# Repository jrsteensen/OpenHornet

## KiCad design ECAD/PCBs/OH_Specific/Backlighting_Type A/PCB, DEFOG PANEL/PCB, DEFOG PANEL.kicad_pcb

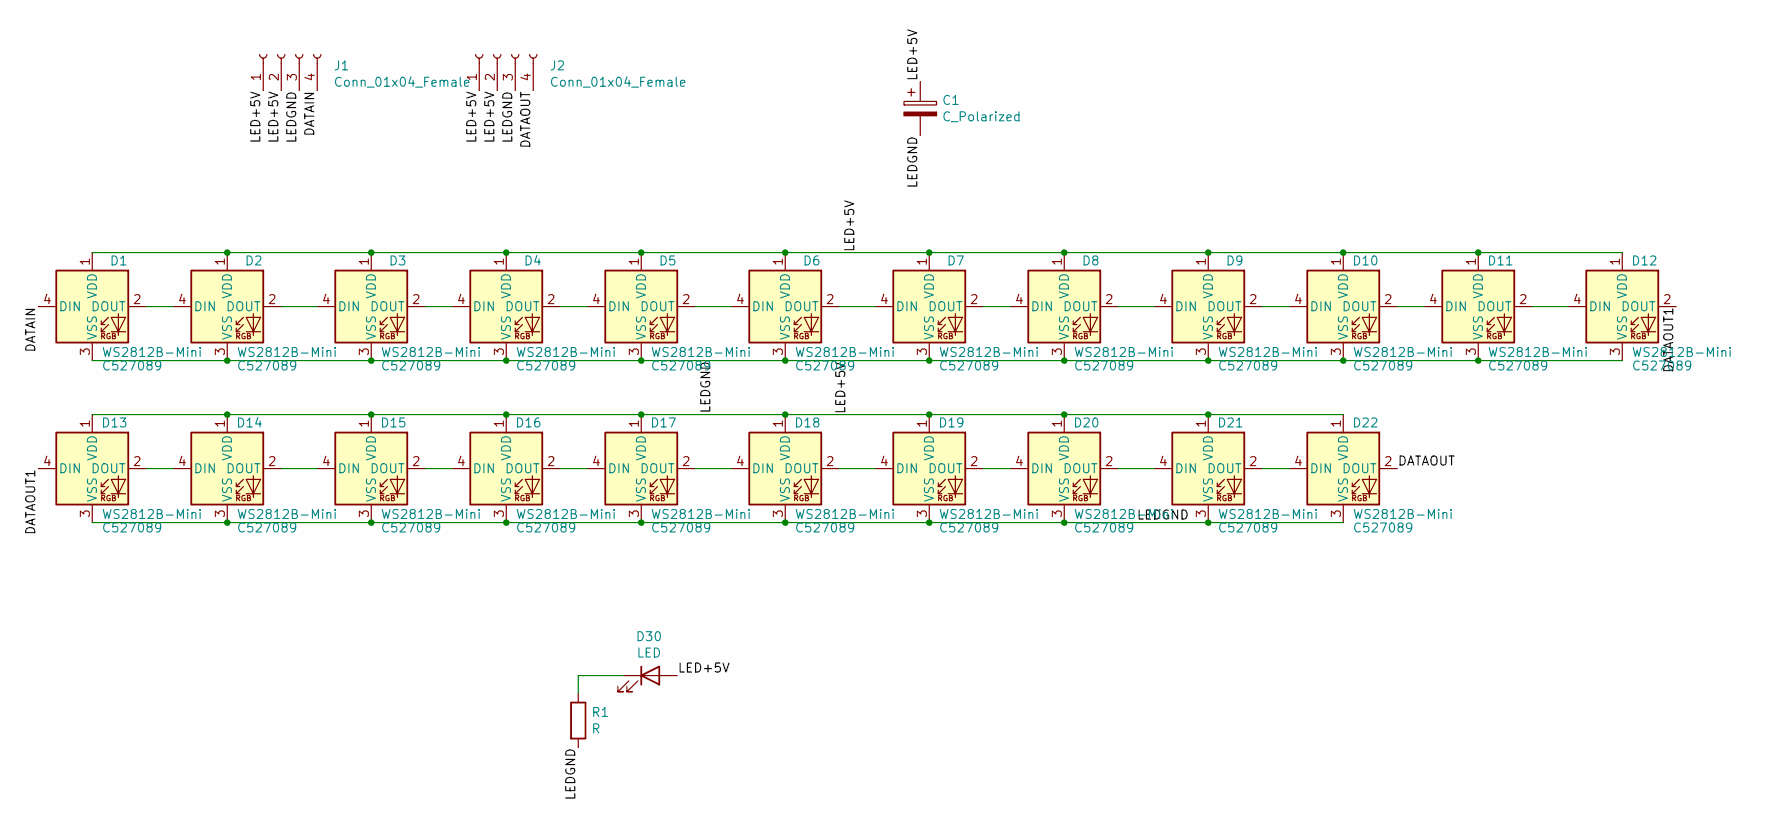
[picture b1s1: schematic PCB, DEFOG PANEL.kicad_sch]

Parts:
C1: C_Polarized; CP_Elec_8x10; LCSC C445083
D1, D2, D3, D4, D5, D6, D7, D8, D9, D10, D11, D12, D13, D14, D15, D16, D17, D18, D19, D20, D21, D22: WS2812B-Mini; LED_WS2812B-MINI_PLCC4_3.5x3.5mm_P1.75mm; LCSC Part Number C527089
D30: LED; LED_D3.0mm
J1, J2: Conn_01x04_Female; Molex_Mini-Fit_Jr_5566-04A_2x02_P4.20mm_Vertical; LCSC C293502
R1: R; R_0603_1608Metric; LCSC C23179

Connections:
/DATAIN: D1.4 (DIN), J1.4
/DATAOUT: D22.2 (DOUT), J2.4
/DATAOUT1: D12.2 (DOUT), D13.4 (DIN)
/LED+5V: C1.1, D1.1 (VDD), D2.1 (VDD), D3.1 (VDD), D4.1 (VDD), D5.1 (VDD), D6.1 (VDD), D7.1 (VDD), D8.1 (VDD), D9.1 (VDD), D10.1 (VDD), D11.1 (VDD), D12.1 (VDD), D13.1 (VDD), D14.1 (VDD), D15.1 (VDD), D16.1 (VDD), D17.1 (VDD), D18.1 (VDD), D19.1 (VDD), D20.1 (VDD), D21.1 (VDD), D22.1 (VDD), D30.2 (A), J1.1, J1.2, J2.1, J2.2
/LEDGND: C1.2, D1.3 (VSS), D2.3 (VSS), D3.3 (VSS), D4.3 (VSS), D5.3 (VSS), D6.3 (VSS), D7.3 (VSS), D8.3 (VSS), D9.3 (VSS), D10.3 (VSS), D11.3 (VSS), D12.3 (VSS), D13.3 (VSS), D14.3 (VSS), D15.3 (VSS), D16.3 (VSS), D17.3 (VSS), D18.3 (VSS), D19.3 (VSS), D20.3 (VSS), D21.3 (VSS), D22.3 (VSS), J1.3, J2.3, R1.2
unnamed: D1.2 (DOUT), D2.4 (DIN)
unnamed: D2.2 (DOUT), D3.4 (DIN)
unnamed: D3.2 (DOUT), D4.4 (DIN)
unnamed: D4.2 (DOUT), D5.4 (DIN)
unnamed: D5.2 (DOUT), D6.4 (DIN)
unnamed: D6.2 (DOUT), D7.4 (DIN)
unnamed: D7.2 (DOUT), D8.4 (DIN)
unnamed: D8.2 (DOUT), D9.4 (DIN)
unnamed: D10.2 (DOUT), D11.4 (DIN)
unnamed: D9.2 (DOUT), D10.4 (DIN)
unnamed: D11.2 (DOUT), D12.4 (DIN)
unnamed: D13.2 (DOUT), D14.4 (DIN)
unnamed: D14.2 (DOUT), D15.4 (DIN)
unnamed: D15.2 (DOUT), D16.4 (DIN)
unnamed: D16.2 (DOUT), D17.4 (DIN)
unnamed: D17.2 (DOUT), D18.4 (DIN)
unnamed: D18.2 (DOUT), D19.4 (DIN)
unnamed: D19.2 (DOUT), D20.4 (DIN)
unnamed: D20.2 (DOUT), D21.4 (DIN)
unnamed: D21.2 (DOUT), D22.4 (DIN)
unnamed: D30.1 (K), R1.1

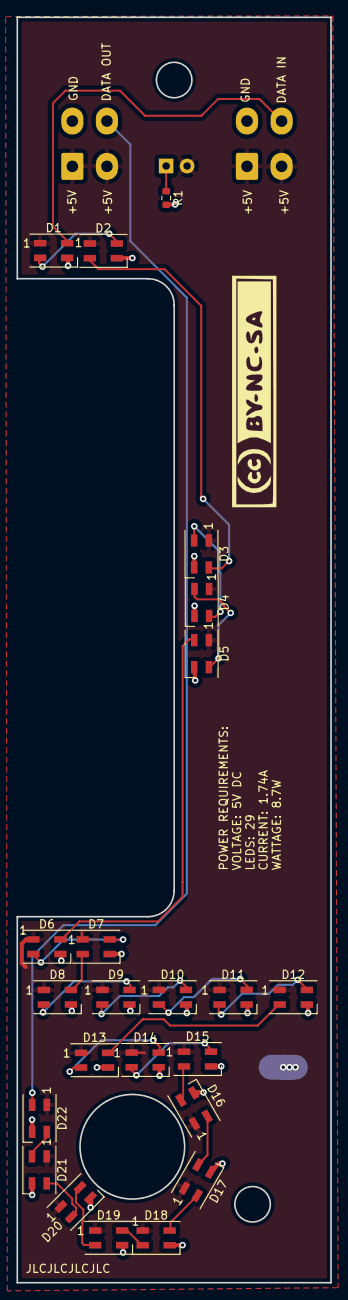
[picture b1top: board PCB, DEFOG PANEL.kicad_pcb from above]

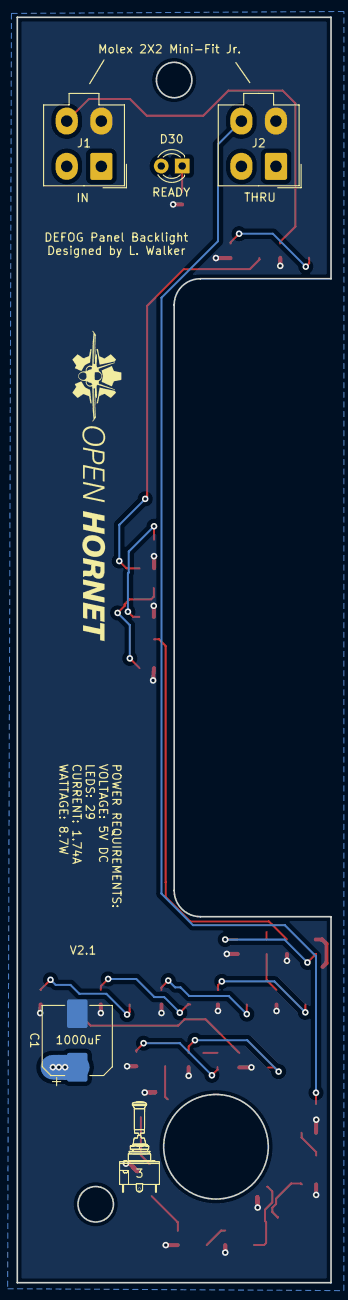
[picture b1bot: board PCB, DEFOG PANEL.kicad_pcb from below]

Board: 2 copper layers, 38.1 x 153.7 mm, 30 parts (5 on the bottom side), 26 nets.

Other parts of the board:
G1: LOGO; CC-BY-NC-SA-Small
G2: S3AL Toggle; S3AL_Toggle_Silkscreen
G3: LOGO; OH_LOGO_37.7mm_5.9mm

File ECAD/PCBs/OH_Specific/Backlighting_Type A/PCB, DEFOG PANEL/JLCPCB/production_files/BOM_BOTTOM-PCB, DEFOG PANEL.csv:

Comment,Designator,Footprint,LCSC
Conn_01x04_Female,"J1,J2",Molex_Mini-Fit_Jr_5566-04A_2x02_P4.20mm_Vertical,C293502
C_Polarized,C1,CP_Elec_8x10,C445083
LED,D30,LED_D3.0mm,

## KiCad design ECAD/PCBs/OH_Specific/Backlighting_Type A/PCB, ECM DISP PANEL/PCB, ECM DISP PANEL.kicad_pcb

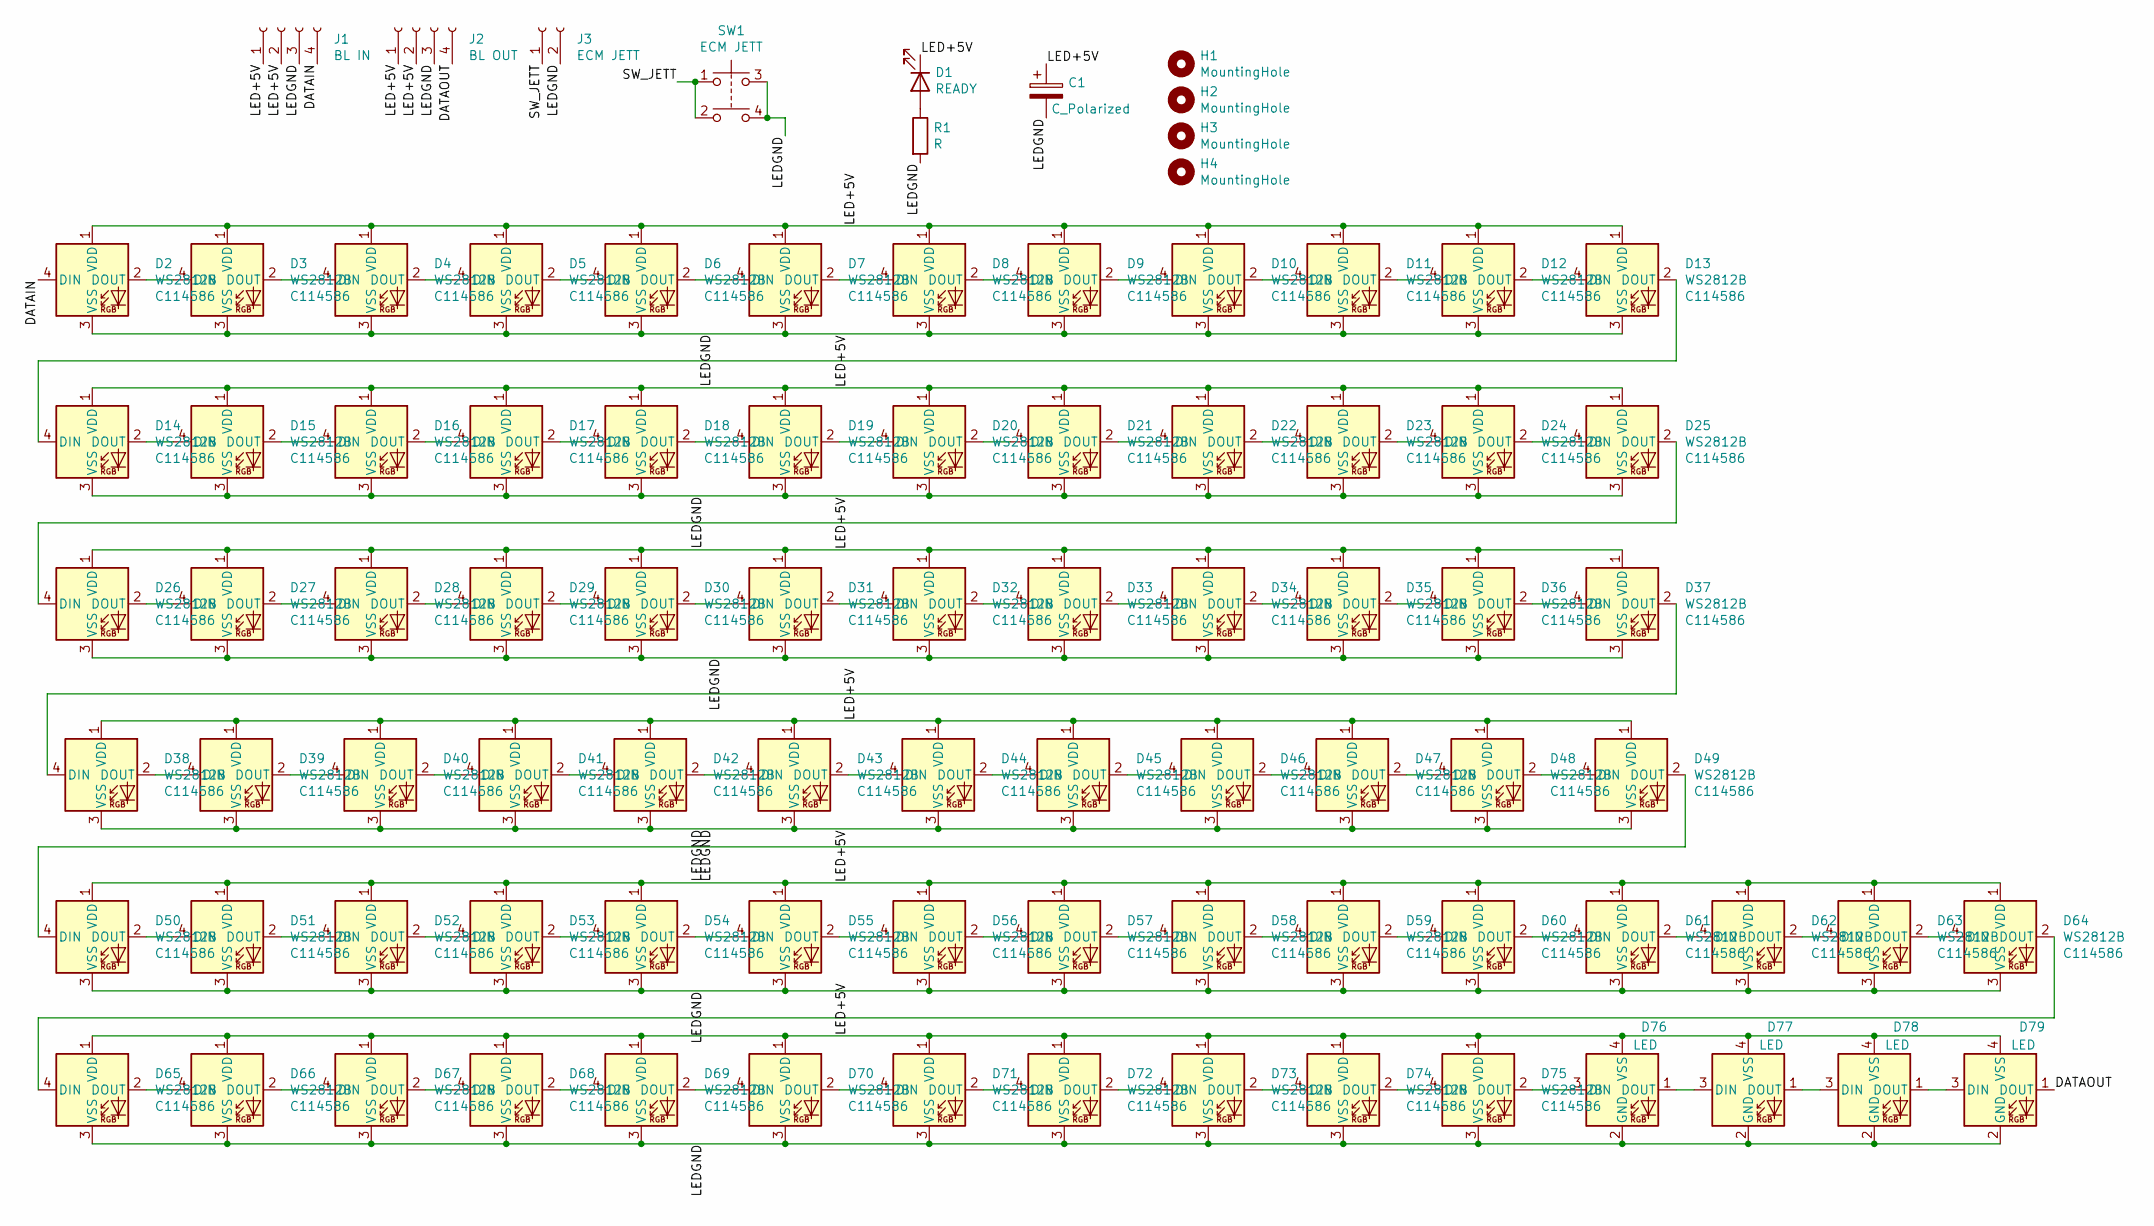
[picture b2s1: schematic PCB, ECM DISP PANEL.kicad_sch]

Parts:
C1: C_Polarized; CP_Elec_8x10
D1: READY; LED_D3.0mm
D2, D3, D4, D5, D6, D7, D8, D9, D10, D11, D12, D13, D14, D15, D16, D17, D18, D19, D20, D21, D22, D23, D24, D25, D26, D27, D28, D29, D30, D31, D32, D33, D34, D35, D36, D37, D38, D39, D40, D41, D42, D43, D44, D45, D46, D47, D48, D49, D50, D51, D52, D53, D54, D55, D56, D57, D58, D59, D60, D61, D62, D63, D64, D65, D66, D67, D68, D69, D70, D71, D72, D73, D74, D75: WS2812B; LED_WS2812B_PLCC4_5.0x5.0mm_P3.2mm; LCSC Part Number C114586
D76, D77, D78, D79: LED; WS2812-2020; LCSC C965555
H1, H2, H3, H4: MountingHole; MountingHole_4.5mm_Pad
J1: BL IN; Molex_Mini-Fit_Jr_5566-04A_2x02_P4.20mm_Vertical
J2: BL OUT; Molex_Mini-Fit_Jr_5566-04A_2x02_P4.20mm_Vertical
J3: ECM JETT; Molex_KK-254_AE-6410-02A_1x02_P2.54mm_Vertical
R1: R; R_0603_1608Metric; LCSC C23138
SW1: ECM JETT; SW_TH_Tactile_Omron_B3F-10xx

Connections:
/DATAIN: D2.4 (DIN), J1.4
/DATAOUT: D79.1 (DOUT), J2.4
/LED+5V: C1.1, D1.1 (K), D2.1 (VDD), D3.1 (VDD), D4.1 (VDD), D5.1 (VDD), D6.1 (VDD), D7.1 (VDD), D8.1 (VDD), D9.1 (VDD), D10.1 (VDD), D11.1 (VDD), D12.1 (VDD), D13.1 (VDD), D14.1 (VDD), D15.1 (VDD), D16.1 (VDD), D17.1 (VDD), D18.1 (VDD), D19.1 (VDD), D20.1 (VDD), D21.1 (VDD), D22.1 (VDD), D23.1 (VDD), D24.1 (VDD), D25.1 (VDD), D26.1 (VDD), D27.1 (VDD), D28.1 (VDD), D29.1 (VDD), D30.1 (VDD), D31.1 (VDD), D32.1 (VDD), D33.1 (VDD), D34.1 (VDD), D35.1 (VDD), D36.1 (VDD), D37.1 (VDD), D38.1 (VDD), D39.1 (VDD), D40.1 (VDD), D41.1 (VDD), D42.1 (VDD), D43.1 (VDD), D44.1 (VDD), D45.1 (VDD), D46.1 (VDD), D47.1 (VDD), D48.1 (VDD), D49.1 (VDD), D50.1 (VDD), D51.1 (VDD), D52.1 (VDD), D53.1 (VDD), D54.1 (VDD), D55.1 (VDD), D56.1 (VDD), D57.1 (VDD), D58.1 (VDD), D59.1 (VDD), D60.1 (VDD), D61.1 (VDD), D62.1 (VDD), D63.1 (VDD), D64.1 (VDD), D65.1 (VDD), D66.1 (VDD), D67.1 (VDD), D68.1 (VDD), D69.1 (VDD), D70.1 (VDD), D71.1 (VDD), D72.1 (VDD), D73.1 (VDD), D74.1 (VDD), D75.1 (VDD), D76.4 (VSS), D77.4 (VSS), D78.4 (VSS), D79.4 (VSS), J1.1, J1.2, J2.1, J2.2
/LEDGND: C1.2, D2.3 (VSS), D3.3 (VSS), D4.3 (VSS), D5.3 (VSS), D6.3 (VSS), D7.3 (VSS), D8.3 (VSS), D9.3 (VSS), D10.3 (VSS), D11.3 (VSS), D12.3 (VSS), D13.3 (VSS), D14.3 (VSS), D15.3 (VSS), D16.3 (VSS), D17.3 (VSS), D18.3 (VSS), D19.3 (VSS), D20.3 (VSS), D21.3 (VSS), D22.3 (VSS), D23.3 (VSS), D24.3 (VSS), D25.3 (VSS), D26.3 (VSS), D27.3 (VSS), D28.3 (VSS), D29.3 (VSS), D30.3 (VSS), D31.3 (VSS), D32.3 (VSS), D33.3 (VSS), D34.3 (VSS), D35.3 (VSS), D36.3 (VSS), D37.3 (VSS), D38.3 (VSS), D39.3 (VSS), D40.3 (VSS), D41.3 (VSS), D42.3 (VSS), D43.3 (VSS), D44.3 (VSS), D45.3 (VSS), D46.3 (VSS), D47.3 (VSS), D48.3 (VSS), D49.3 (VSS), D50.3 (VSS), D51.3 (VSS), D52.3 (VSS), D53.3 (VSS), D54.3 (VSS), D55.3 (VSS), D56.3 (VSS), D57.3 (VSS), D58.3 (VSS), D59.3 (VSS), D60.3 (VSS), D61.3 (VSS), D62.3 (VSS), D63.3 (VSS), D64.3 (VSS), D65.3 (VSS), D66.3 (VSS), D67.3 (VSS), D68.3 (VSS), D69.3 (VSS), D70.3 (VSS), D71.3 (VSS), D72.3 (VSS), D73.3 (VSS), D74.3 (VSS), D75.3 (VSS), D76.2 (GND), D77.2 (GND), D78.2 (GND), D79.2 (GND), J1.3, J2.3, J3.2, R1.2, SW1.3, SW1.4
/SW_JETT: J3.1, SW1.1, SW1.2
unnamed: D1.2 (A), R1.1
unnamed: D2.2 (DOUT), D3.4 (DIN)
unnamed: D3.2 (DOUT), D4.4 (DIN)
unnamed: D4.2 (DOUT), D5.4 (DIN)
unnamed: D5.2 (DOUT), D6.4 (DIN)
unnamed: D6.2 (DOUT), D7.4 (DIN)
unnamed: D7.2 (DOUT), D8.4 (DIN)
unnamed: D8.2 (DOUT), D9.4 (DIN)
unnamed: D10.2 (DOUT), D11.4 (DIN)
unnamed: D9.2 (DOUT), D10.4 (DIN)
unnamed: D11.2 (DOUT), D12.4 (DIN)
unnamed: D12.2 (DOUT), D13.4 (DIN)
unnamed: D13.2 (DOUT), D14.4 (DIN)
unnamed: D14.2 (DOUT), D15.4 (DIN)
unnamed: D15.2 (DOUT), D16.4 (DIN)
unnamed: D16.2 (DOUT), D17.4 (DIN)
unnamed: D17.2 (DOUT), D18.4 (DIN)
unnamed: D18.2 (DOUT), D19.4 (DIN)
unnamed: D19.2 (DOUT), D20.4 (DIN)
unnamed: D20.2 (DOUT), D21.4 (DIN)
unnamed: D21.2 (DOUT), D22.4 (DIN)
unnamed: D22.2 (DOUT), D23.4 (DIN)
unnamed: D23.2 (DOUT), D24.4 (DIN)
unnamed: D24.2 (DOUT), D25.4 (DIN)
unnamed: D25.2 (DOUT), D26.4 (DIN)
unnamed: D26.2 (DOUT), D27.4 (DIN)
unnamed: D27.2 (DOUT), D28.4 (DIN)
unnamed: D28.2 (DOUT), D29.4 (DIN)
unnamed: D29.2 (DOUT), D30.4 (DIN)
unnamed: D30.2 (DOUT), D31.4 (DIN)
unnamed: D31.2 (DOUT), D32.4 (DIN)
unnamed: D32.2 (DOUT), D33.4 (DIN)
unnamed: D33.2 (DOUT), D34.4 (DIN)
unnamed: D34.2 (DOUT), D35.4 (DIN)
unnamed: D35.2 (DOUT), D36.4 (DIN)
unnamed: D36.2 (DOUT), D37.4 (DIN)
unnamed: D37.2 (DOUT), D38.4 (DIN)
unnamed: D38.2 (DOUT), D39.4 (DIN)
unnamed: D39.2 (DOUT), D40.4 (DIN)
unnamed: D40.2 (DOUT), D41.4 (DIN)
unnamed: D41.2 (DOUT), D42.4 (DIN)
unnamed: D42.2 (DOUT), D43.4 (DIN)
unnamed: D43.2 (DOUT), D44.4 (DIN)
unnamed: D44.2 (DOUT), D45.4 (DIN)
unnamed: D45.2 (DOUT), D46.4 (DIN)
unnamed: D46.2 (DOUT), D47.4 (DIN)
unnamed: D47.2 (DOUT), D48.4 (DIN)
unnamed: D48.2 (DOUT), D49.4 (DIN)
unnamed: D49.2 (DOUT), D50.4 (DIN)
unnamed: D50.2 (DOUT), D51.4 (DIN)
unnamed: D51.2 (DOUT), D52.4 (DIN)
unnamed: D52.2 (DOUT), D53.4 (DIN)
unnamed: D53.2 (DOUT), D54.4 (DIN)
unnamed: D54.2 (DOUT), D55.4 (DIN)
unnamed: D55.2 (DOUT), D56.4 (DIN)
unnamed: D56.2 (DOUT), D57.4 (DIN)
unnamed: D57.2 (DOUT), D58.4 (DIN)
unnamed: D58.2 (DOUT), D59.4 (DIN)
unnamed: D59.2 (DOUT), D60.4 (DIN)
unnamed: D60.2 (DOUT), D61.4 (DIN)
unnamed: D61.2 (DOUT), D62.4 (DIN)
unnamed: D62.2 (DOUT), D63.4 (DIN)
unnamed: D63.2 (DOUT), D64.4 (DIN)
unnamed: D64.2 (DOUT), D65.4 (DIN)
unnamed: D65.2 (DOUT), D66.4 (DIN)
unnamed: D66.2 (DOUT), D67.4 (DIN)
unnamed: D67.2 (DOUT), D68.4 (DIN)
unnamed: D68.2 (DOUT), D69.4 (DIN)
unnamed: D69.2 (DOUT), D70.4 (DIN)
unnamed: D70.2 (DOUT), D71.4 (DIN)
unnamed: D71.2 (DOUT), D72.4 (DIN)
unnamed: D72.2 (DOUT), D73.4 (DIN)
unnamed: D73.2 (DOUT), D74.4 (DIN)
unnamed: D74.2 (DOUT), D75.4 (DIN)
unnamed: D75.2 (DOUT), D76.3 (DIN)
unnamed: D76.1 (DOUT), D77.3 (DIN)
unnamed: D77.1 (DOUT), D78.3 (DIN)
unnamed: D78.1 (DOUT), D79.3 (DIN)

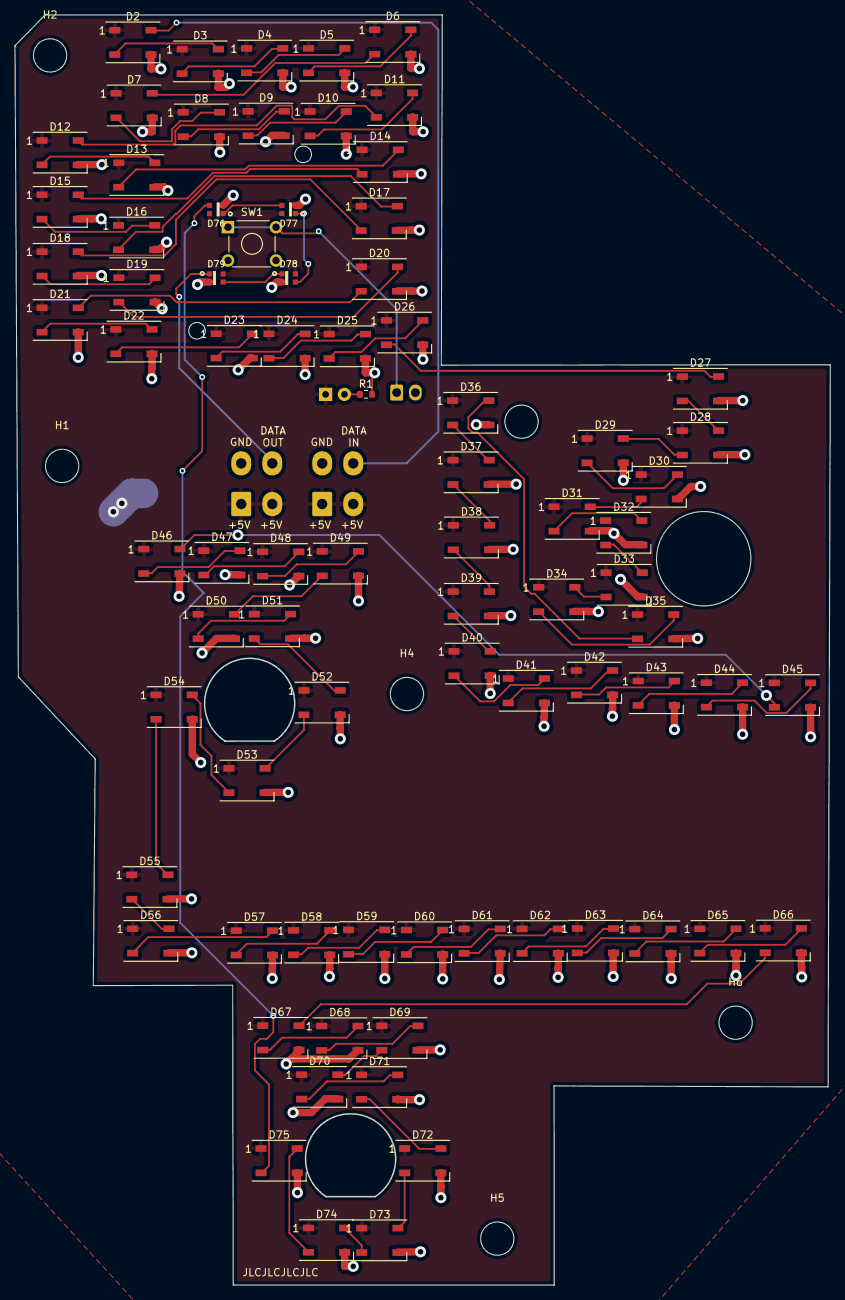
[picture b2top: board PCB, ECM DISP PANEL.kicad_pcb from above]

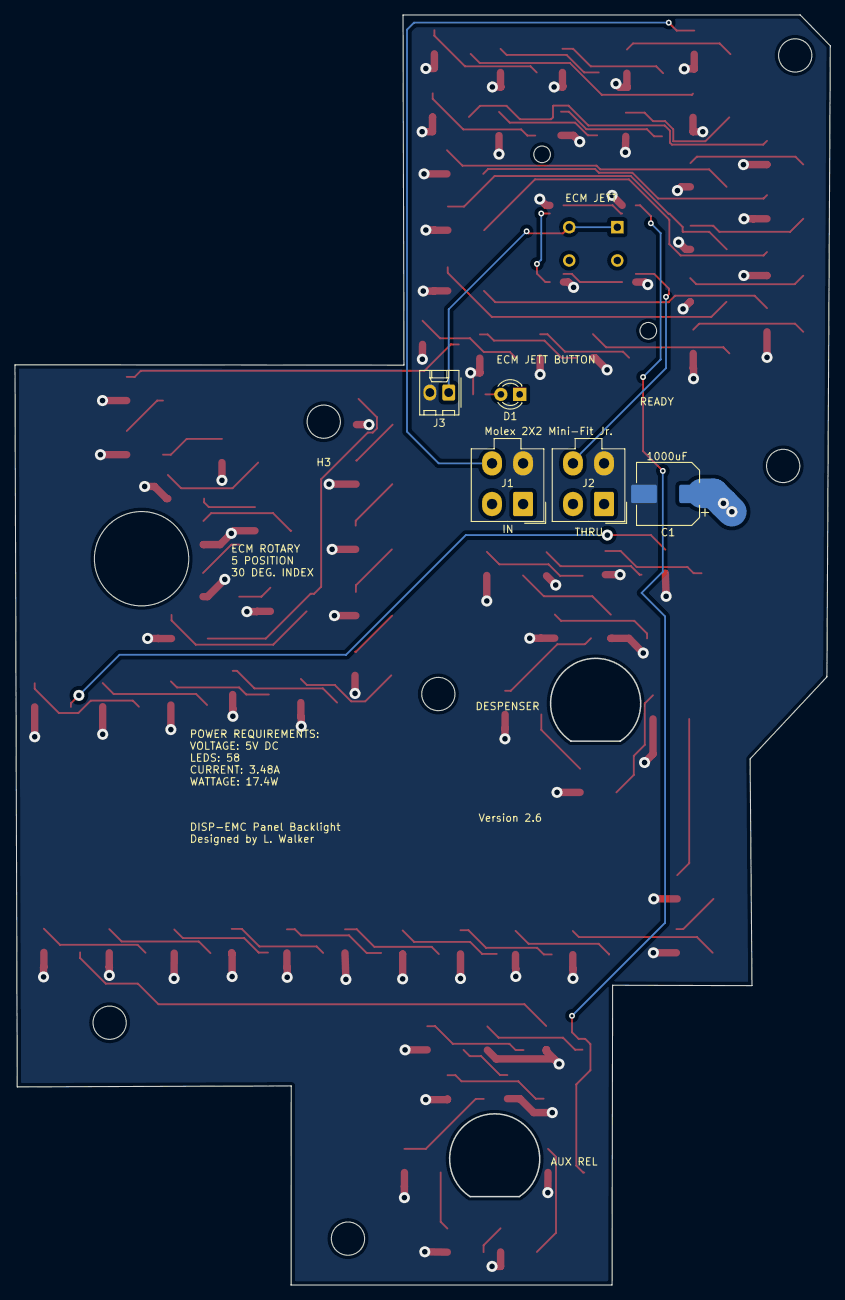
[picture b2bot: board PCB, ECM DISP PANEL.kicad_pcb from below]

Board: 2 copper layers, 110.3 x 171.8 mm, 91 parts (6 on the bottom side), 83 nets.

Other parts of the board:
H5, H6: MountingHole; MountingHole_4.5mm

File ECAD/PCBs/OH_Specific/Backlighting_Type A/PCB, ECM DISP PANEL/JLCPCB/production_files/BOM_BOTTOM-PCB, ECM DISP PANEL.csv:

Comment,Designator,Footprint,LCSC
ECM JETT,J3,Molex_KK-254_AE-6410-02A_1x02_P2.54mm_Vertical,C293316
BL IN,"J1,J2",Molex_Mini-Fit_Jr_5566-04A_2x02_P4.20mm_Vertical,C293502
1000 nF,C1,CP_Elec_8x10,C445083
READY,D1,LED_D3.0mm,

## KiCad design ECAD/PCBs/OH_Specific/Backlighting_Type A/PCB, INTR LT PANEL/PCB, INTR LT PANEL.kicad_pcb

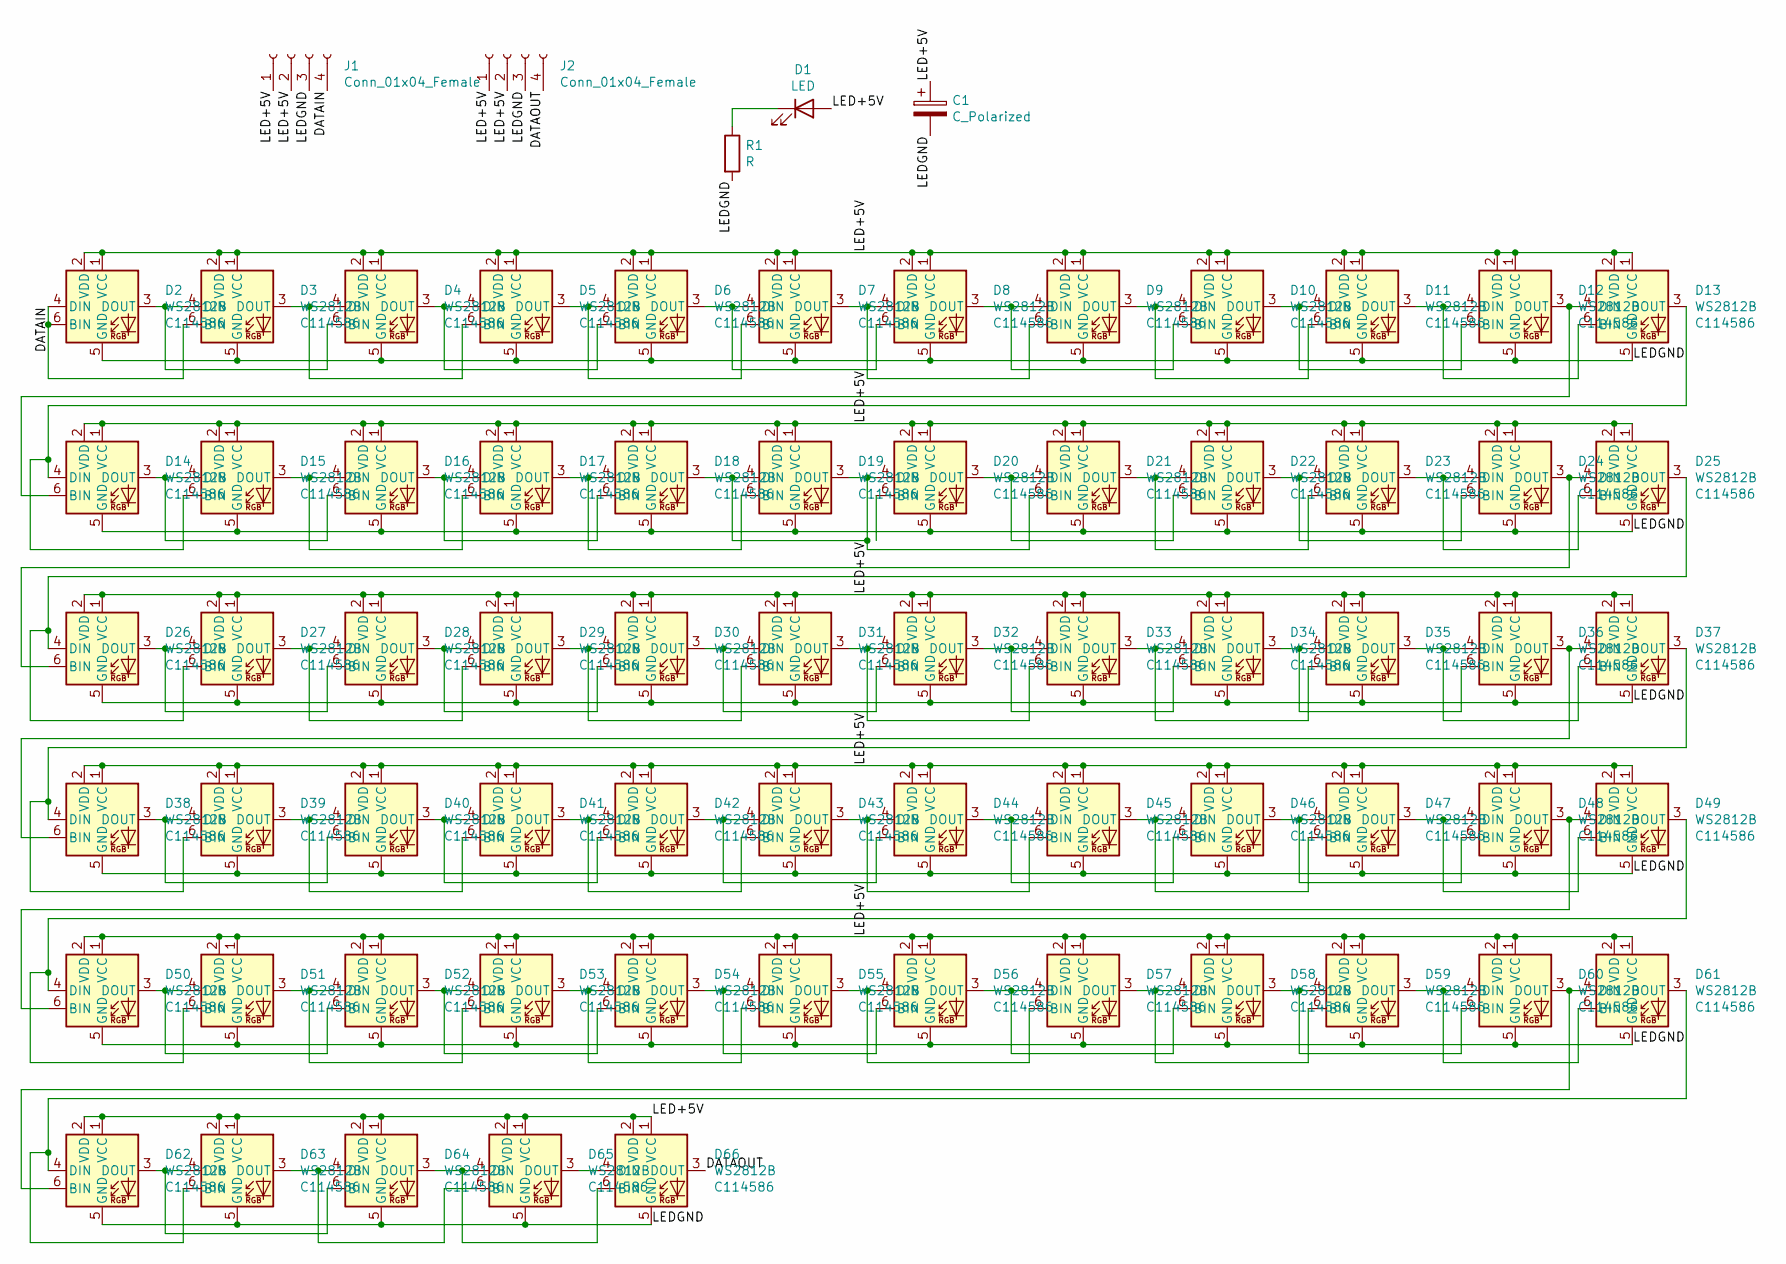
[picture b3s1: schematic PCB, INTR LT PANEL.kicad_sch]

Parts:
C1: C_Polarized; CP_Elec_8x10
D1: LED; LED_D3.0mm
D2, D3, D4, D5, D6, D7, D8, D9, D10, D11, D12, D13, D14, D15, D16, D17, D18, D19, D20, D21, D22, D23, D24, D25, D26, D27, D28, D29, D30, D31, D32, D33, D34, D35, D36, D37, D38, D39, D40, D41, D42, D43, D44, D45, D46, D47, D48, D49, D50, D51, D52, D53, D54, D55, D56, D57, D58, D59, D60, D61, D62, D63, D64, D65, D66: WS2812B; LED_WS2812_PLCC6_5.0x5.0mm_P1.6mm; LCSC Part Number C114586
J1, J2: Conn_01x04_Female; Molex_Mini-Fit_Jr_5566-04A_2x02_P4.20mm_Vertical
R1: R; R_0603_1608Metric

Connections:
/DATAIN: D2.4 (DIN), D2.6 (BIN), D3.6 (BIN), J1.4
/DATAOUT: D66.3 (DOUT), J2.4
/LED+5V: C1.1, D1.2 (A), D2.1 (VCC), D2.2 (VDD), D3.1 (VCC), D3.2 (VDD), D4.1 (VCC), D4.2 (VDD), D5.1 (VCC), D5.2 (VDD), D6.1 (VCC), D6.2 (VDD), D7.1 (VCC), D7.2 (VDD), D8.1 (VCC), D8.2 (VDD), D9.1 (VCC), D9.2 (VDD), D10.1 (VCC), D10.2 (VDD), D11.1 (VCC), D11.2 (VDD), D12.1 (VCC), D12.2 (VDD), D13.1 (VCC), D13.2 (VDD), D14.1 (VCC), D14.2 (VDD), D15.1 (VCC), D15.2 (VDD), D16.1 (VCC), D16.2 (VDD), D17.1 (VCC), D17.2 (VDD), D18.1 (VCC), D18.2 (VDD), D19.1 (VCC), D19.2 (VDD), D20.1 (VCC), D20.2 (VDD), D21.1 (VCC), D21.2 (VDD), D22.1 (VCC), D22.2 (VDD), D23.1 (VCC), D23.2 (VDD), D24.1 (VCC), D24.2 (VDD), D25.1 (VCC), D25.2 (VDD), D26.1 (VCC), D26.2 (VDD), D27.1 (VCC), D27.2 (VDD), D28.1 (VCC), D28.2 (VDD), D29.1 (VCC), D29.2 (VDD), D30.1 (VCC), D30.2 (VDD), D31.1 (VCC), D31.2 (VDD), D32.1 (VCC), D32.2 (VDD), D33.1 (VCC), D33.2 (VDD), D34.1 (VCC), D34.2 (VDD), D35.1 (VCC), D35.2 (VDD), D36.1 (VCC), D36.2 (VDD), D37.1 (VCC), D37.2 (VDD), D38.1 (VCC), D38.2 (VDD), D39.1 (VCC), D39.2 (VDD), D40.1 (VCC), D40.2 (VDD), D41.1 (VCC), D41.2 (VDD), D42.1 (VCC), D42.2 (VDD), D43.1 (VCC), D43.2 (VDD), D44.1 (VCC), D44.2 (VDD), D45.1 (VCC), D45.2 (VDD), D46.1 (VCC), D46.2 (VDD), D47.1 (VCC), D47.2 (VDD), D48.1 (VCC), D48.2 (VDD), D49.1 (VCC), D49.2 (VDD), D50.1 (VCC), D50.2 (VDD), D51.1 (VCC), D51.2 (VDD), D52.1 (VCC), D52.2 (VDD), D53.1 (VCC), D53.2 (VDD), D54.1 (VCC), D54.2 (VDD), D55.1 (VCC), D55.2 (VDD), D56.1 (VCC), D56.2 (VDD), D57.1 (VCC), D57.2 (VDD), D58.1 (VCC), D58.2 (VDD), D59.1 (VCC), D59.2 (VDD), D60.1 (VCC), D60.2 (VDD), D61.1 (VCC), D61.2 (VDD), D62.1 (VCC), D62.2 (VDD), D63.1 (VCC), D63.2 (VDD), D64.1 (VCC), D64.2 (VDD), D65.1 (VCC), D65.2 (VDD), D66.1 (VCC), D66.2 (VDD), J1.1, J1.2, J2.1, J2.2
/LEDGND: C1.2, D2.5 (GND), D3.5 (GND), D4.5 (GND), D5.5 (GND), D6.5 (GND), D7.5 (GND), D8.5 (GND), D9.5 (GND), D10.5 (GND), D11.5 (GND), D12.5 (GND), D13.5 (GND), D14.5 (GND), D15.5 (GND), D16.5 (GND), D17.5 (GND), D18.5 (GND), D19.5 (GND), D20.5 (GND), D21.5 (GND), D22.5 (GND), D23.5 (GND), D24.5 (GND), D25.5 (GND), D26.5 (GND), D27.5 (GND), D28.5 (GND), D29.5 (GND), D30.5 (GND), D31.5 (GND), D32.5 (GND), D33.5 (GND), D34.5 (GND), D35.5 (GND), D36.5 (GND), D37.5 (GND), D38.5 (GND), D39.5 (GND), D40.5 (GND), D41.5 (GND), D42.5 (GND), D43.5 (GND), D44.5 (GND), D45.5 (GND), D46.5 (GND), D47.5 (GND), D48.5 (GND), D49.5 (GND), D50.5 (GND), D51.5 (GND), D52.5 (GND), D53.5 (GND), D54.5 (GND), D55.5 (GND), D56.5 (GND), D57.5 (GND), D58.5 (GND), D59.5 (GND), D60.5 (GND), D61.5 (GND), D62.5 (GND), D63.5 (GND), D64.5 (GND), D65.5 (GND), D66.5 (GND), J1.3, J2.3, R1.2
unnamed: D1.1 (K), R1.1
unnamed: D2.3 (DOUT), D3.4 (DIN), D4.6 (BIN)
unnamed: D3.3 (DOUT), D4.4 (DIN), D5.6 (BIN)
unnamed: D4.3 (DOUT), D5.4 (DIN), D6.6 (BIN)
unnamed: D5.3 (DOUT), D6.4 (DIN), D7.6 (BIN)
unnamed: D6.3 (DOUT), D7.4 (DIN), D8.6 (BIN)
unnamed: D7.3 (DOUT), D8.4 (DIN), D9.6 (BIN)
unnamed: D10.3 (DOUT), D11.4 (DIN), D12.6 (BIN)
unnamed: D9.3 (DOUT), D10.4 (DIN), D11.6 (BIN)
unnamed: D8.3 (DOUT), D9.4 (DIN), D10.6 (BIN)
unnamed: D11.3 (DOUT), D12.4 (DIN), D13.6 (BIN)
unnamed: D12.3 (DOUT), D13.4 (DIN), D14.6 (BIN)
unnamed: D13.3 (DOUT), D14.4 (DIN), D15.6 (BIN)
unnamed: D14.3 (DOUT), D15.4 (DIN), D16.6 (BIN)
unnamed: D15.3 (DOUT), D16.4 (DIN), D17.6 (BIN)
unnamed: D16.3 (DOUT), D17.4 (DIN), D18.6 (BIN)
unnamed: D17.3 (DOUT), D18.4 (DIN), D19.6 (BIN)
unnamed: D18.3 (DOUT), D19.3 (DOUT), D19.4 (DIN), D20.4 (DIN), D21.6 (BIN)
unnamed: D20.3 (DOUT), D21.4 (DIN), D22.6 (BIN)
unnamed: D21.3 (DOUT), D22.4 (DIN), D23.6 (BIN)
unnamed: D22.3 (DOUT), D23.4 (DIN), D24.6 (BIN)
unnamed: D23.3 (DOUT), D24.4 (DIN), D25.6 (BIN)
unnamed: D24.3 (DOUT), D25.4 (DIN), D26.6 (BIN)
unnamed: D25.3 (DOUT), D26.4 (DIN), D27.6 (BIN)
unnamed: D26.3 (DOUT), D27.4 (DIN), D28.6 (BIN)
unnamed: D27.3 (DOUT), D28.4 (DIN), D29.6 (BIN)
unnamed: D28.3 (DOUT), D29.4 (DIN), D30.6 (BIN)
unnamed: D29.3 (DOUT), D30.4 (DIN), D31.6 (BIN)
unnamed: D30.3 (DOUT), D31.4 (DIN), D32.6 (BIN)
unnamed: D31.3 (DOUT), D32.4 (DIN), D33.6 (BIN)
unnamed: D32.3 (DOUT), D33.4 (DIN), D34.6 (BIN)
unnamed: D33.3 (DOUT), D34.4 (DIN), D35.6 (BIN)
unnamed: D34.3 (DOUT), D35.4 (DIN), D36.6 (BIN)
unnamed: D35.3 (DOUT), D36.4 (DIN), D37.6 (BIN)
unnamed: D36.3 (DOUT), D37.4 (DIN), D38.6 (BIN)
unnamed: D37.3 (DOUT), D38.4 (DIN), D39.6 (BIN)
unnamed: D38.3 (DOUT), D39.4 (DIN), D40.6 (BIN)
unnamed: D39.3 (DOUT), D40.4 (DIN), D41.6 (BIN)
unnamed: D40.3 (DOUT), D41.4 (DIN), D42.6 (BIN)
unnamed: D41.3 (DOUT), D42.4 (DIN), D43.6 (BIN)
unnamed: D42.3 (DOUT), D43.4 (DIN), D44.6 (BIN)
unnamed: D43.3 (DOUT), D44.4 (DIN), D45.6 (BIN)
unnamed: D44.3 (DOUT), D45.4 (DIN), D46.6 (BIN)
unnamed: D45.3 (DOUT), D46.4 (DIN), D47.6 (BIN)
unnamed: D46.3 (DOUT), D47.4 (DIN), D48.6 (BIN)
unnamed: D47.3 (DOUT), D48.4 (DIN), D49.6 (BIN)
unnamed: D48.3 (DOUT), D49.4 (DIN), D50.6 (BIN)
unnamed: D49.3 (DOUT), D50.4 (DIN), D51.6 (BIN)
unnamed: D50.3 (DOUT), D51.4 (DIN), D52.6 (BIN)
unnamed: D51.3 (DOUT), D52.4 (DIN), D53.6 (BIN)
unnamed: D52.3 (DOUT), D53.4 (DIN), D54.6 (BIN)
unnamed: D53.3 (DOUT), D54.4 (DIN), D55.6 (BIN)
unnamed: D54.3 (DOUT), D55.4 (DIN), D56.6 (BIN)
unnamed: D55.3 (DOUT), D56.4 (DIN), D57.6 (BIN)
unnamed: D56.3 (DOUT), D57.4 (DIN), D58.6 (BIN)
unnamed: D57.3 (DOUT), D58.4 (DIN), D59.6 (BIN)
unnamed: D58.3 (DOUT), D59.4 (DIN), D60.6 (BIN)
unnamed: D59.3 (DOUT), D60.4 (DIN), D61.6 (BIN)
unnamed: D60.3 (DOUT), D61.4 (DIN), D62.6 (BIN)
unnamed: D61.3 (DOUT), D62.4 (DIN), D63.6 (BIN)
unnamed: D62.3 (DOUT), D63.4 (DIN), D64.6 (BIN)
unnamed: D63.3 (DOUT), D64.4 (DIN), D65.6 (BIN)
unnamed: D64.3 (DOUT), D65.4 (DIN), D66.6 (BIN)
unnamed: D65.3 (DOUT), D66.4 (DIN)

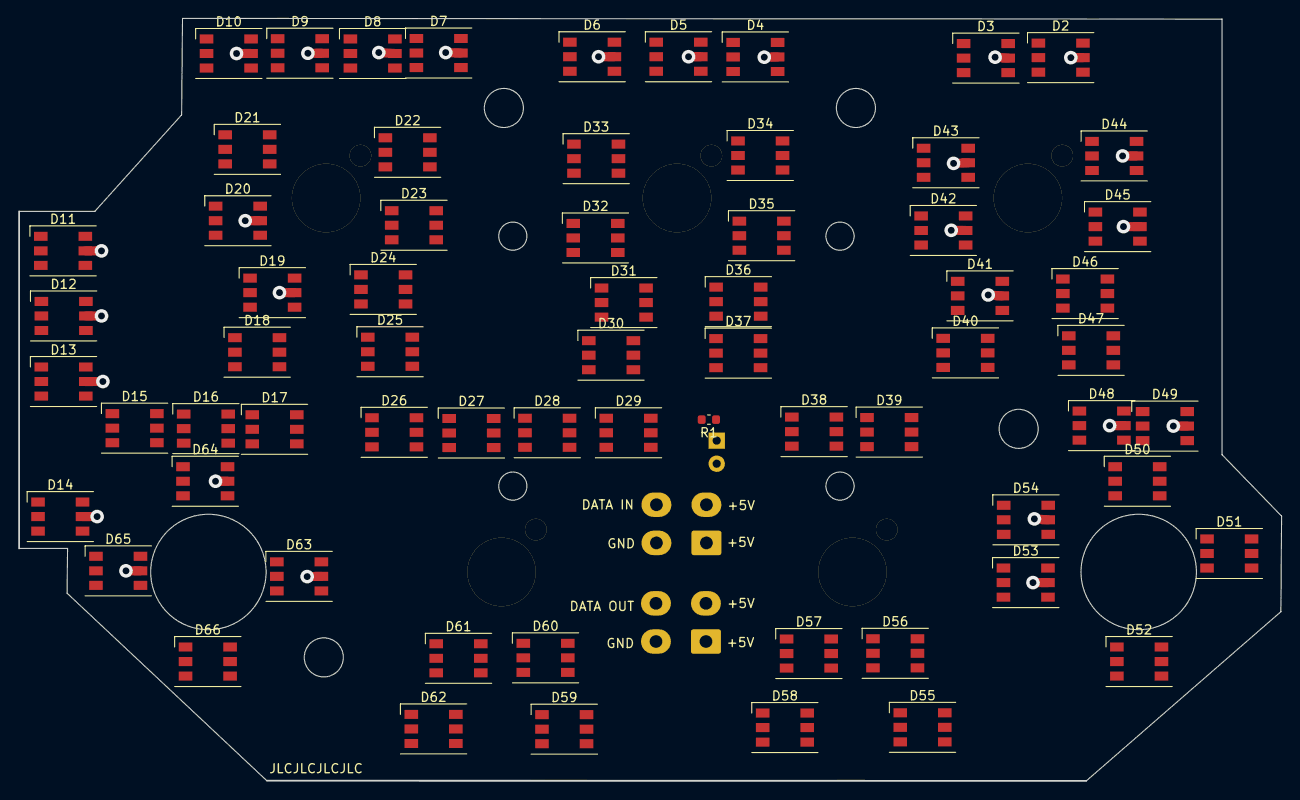
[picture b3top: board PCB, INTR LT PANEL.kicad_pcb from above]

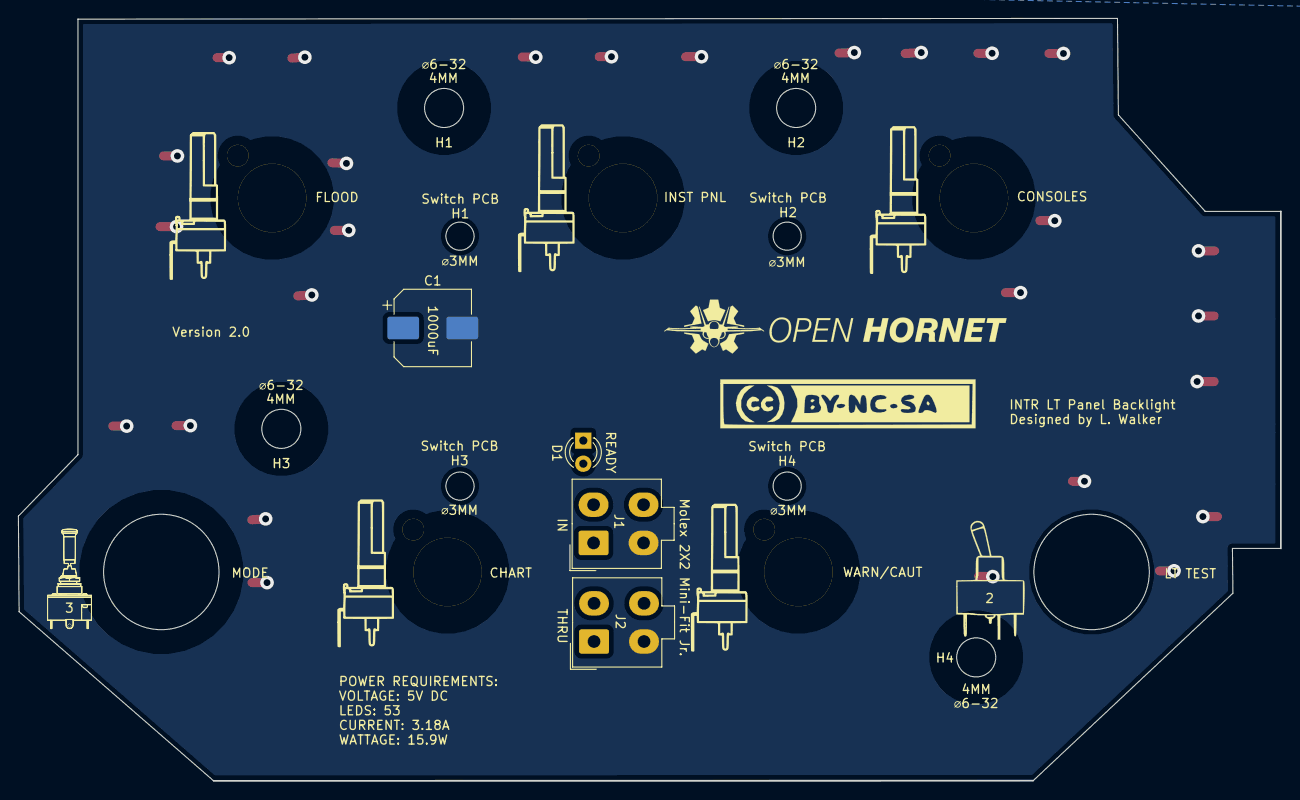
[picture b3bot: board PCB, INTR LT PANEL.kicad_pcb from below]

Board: 2 copper layers, 138.9 x 83.9 mm, 90 parts (13 on the bottom side), 68 nets.

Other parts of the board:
1, 2, 3, 4: OH_Panel_Fastner_Keepout; OH_Panel_6-32_PHS
5, 6, 7, 9, 10: BR10K_Pot_11mm_x_11mm
8: 631H_Toggle_13mm_x_13mm
11: SxAL_Toggle_13x13mm
G1: LOGO; 631HToggle
G2, G3, G4, G6, G7: LOGO; BR10K_Pot_Silkscreen
G5: LOGO; S3ALToggle
G8: LOGO; OH_LOGO_37.7mm_5.9mm
G9: LOGO; CC-BY-NC-SA-Small
